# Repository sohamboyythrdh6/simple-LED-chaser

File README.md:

# simple-LED-chaser
This project is a simple LED chaser circuit using the NE555 timer IC and CD4017 decade counter. The LEDs light up sequentially, creating a running light effect.
And I made this project to learn PCB design and understand how timing circuits and counters work together. It helped me practice using KiCad and designing a real circuit that can be manufactured.

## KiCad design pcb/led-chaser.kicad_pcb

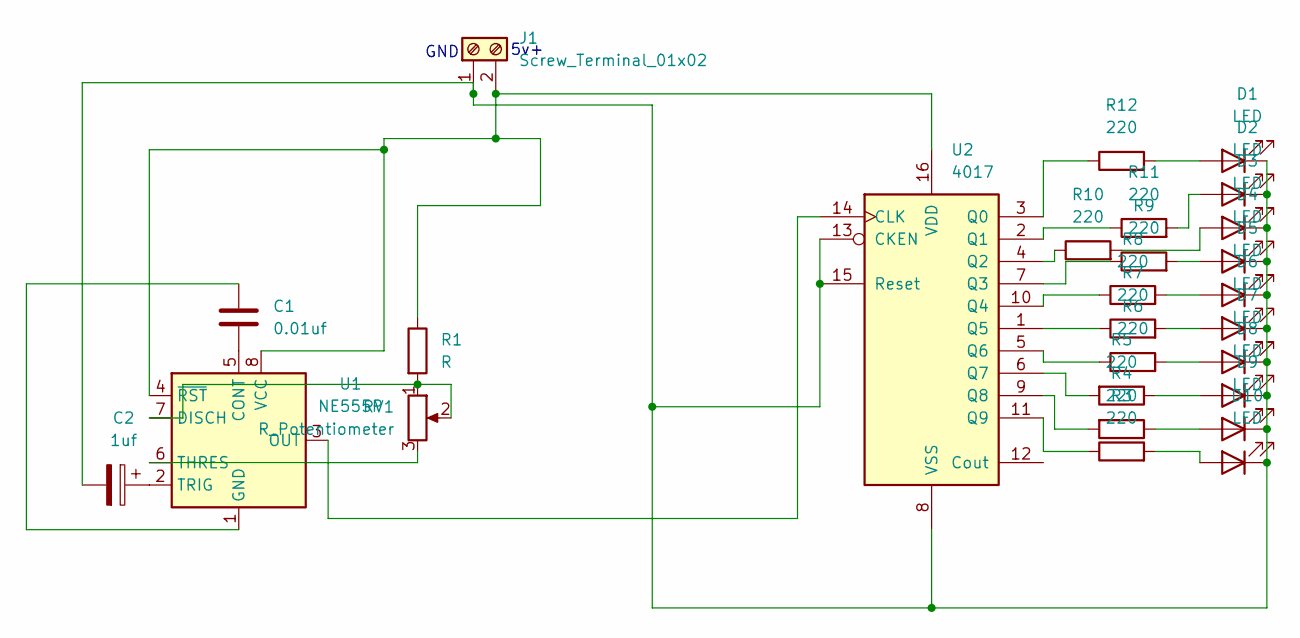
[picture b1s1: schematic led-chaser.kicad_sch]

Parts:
C1: 0.01uf; C_Disc_D7.5mm_W2.5mm_P5.00mm
C2: 1uf; CP_Radial_D5.0mm_P2.50mm
D1, D2, D3, D4, D5, D6, D7, D8, D9, D10: LED; LED_D3.0mm
J1: Screw_Terminal_01x02; TerminalBlock_Phoenix_PT-1,5-2-5.0-H_1x02_P5.00mm_Horizontal
R1: R; R_Axial_DIN0207_L6.3mm_D2.5mm_P2.54mm_Vertical
R3, R4, R5, R6, R7, R8, R9, R10, R11, R12: 220; R_Axial_DIN0207_L6.3mm_D2.5mm_P7.62mm_Horizontal
RV1: R_Potentiometer; Potentiometer_Vishay_T93YA_Vertical
U1: NE555P; DIP-8_W7.62mm
U2: 4017; DIP-16_W7.62mm

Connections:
unnamed: D1.2 (A), R12.2
unnamed: C2.2, D1.1 (K), D2.1 (K), D3.1 (K), D4.1 (K), D5.1 (K), D6.1 (K), D7.1 (K), D8.1 (K), D9.1 (K), D10.1 (K), J1.1, U2.8 (VSS), U2.13 (CKEN), U2.15 (Reset)
unnamed: D2.2 (A), R11.2
unnamed: D3.2 (A), R10.2
unnamed: D4.2 (A), R9.2
unnamed: D5.2 (A), R8.2
unnamed: D6.2 (A), R7.2
unnamed: D7.2 (A), R6.2
unnamed: D8.2 (A), R5.1
unnamed: D9.2 (A), R4.1
unnamed: D10.2 (A), R3.2
unnamed: J1.2, R1.1, U1.4 (~RST), U1.8 (VCC), U2.16 (VDD)
unnamed: C1.2, U1.5 (CONT)
unnamed: R1.2, RV1.1, RV1.2, U1.7 (DISCH)
unnamed: C1.1, U1.1 (GND)
unnamed: U1.3 (OUT), U2.14 (CLK)
unnamed: RV1.3, U1.6 (THRES)
unnamed: C2.1, U1.2 (TRIG)
unnamed: R12.1, U2.3 (Q0)
unnamed: R11.1, U2.2 (Q1)
unnamed: R10.1, U2.4 (Q2)
unnamed: R9.1, U2.7 (Q3)
unnamed: R8.1, U2.10 (Q4)
unnamed: R7.1, U2.1 (Q5)
unnamed: R6.1, U2.5 (Q6)
unnamed: R5.2, U2.6 (Q7)
unnamed: R4.2, U2.9 (Q8)
unnamed: R3.1, U2.11 (Q9)

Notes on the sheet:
GND
5v+

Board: 2 copper layers, 27 parts (0 on the bottom side), 28 nets, no tracks yet.

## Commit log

2026-03-27 Create Diagram
2026-03-27 Create Components
2026-03-31 Create cost
2026-04-01 Update Components
2026-04-01 Update cost
2026-04-05 Create pcb
2026-04-05 Update pcb
2026-04-05 Rename Screenshot 2026-04-01 165849.png to pcb.png
2026-04-05 Add BOM.csv with component list and quantities
